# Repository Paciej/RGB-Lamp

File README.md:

# Smart RGB LED Lamp — BLE Controlled (ESP32)

A Bluetooth Low Energy (BLE) controlled RGB LED lamp built on the ESP32 microcontroller.
The lamp supports multiple lighting modes, real-time color and brightness control,
and temperature monitoring — all controllable wirelessly via **nRF Connect** app.
A dedicated mobile application is currently under development.

---

## PCB Design (Eagle)

> Schematic and board layout designed in Eagle CAD.

---

## Printed & Assembled PCB

> Physical PCB after printing and soldering.

---

## Control via nRF Connect

> The lamp is currently controlled using the **nRF Connect** mobile app.
> Temperature readings are exposed as a BLE characteristic and visible directly in the app.

---

##  Lighting Modes

### Random Color — Physical Button
> Press the physical button to apply a random color using ESP32's hardware RNG.

---

### Candle Mode
> Simulates a realistic flickering candle effect.

---

### Pulse Mode
> Smooth brightness breathing effect.

---

### Wave Mode
> Seamless smooth transitions across the full RGB spectrum.

---

##  Features

-  **Full RGB color control** — set any color via BLE (values 0–255 per channel)
-  **Brightness control** via MOSFET PWM (low-side configuration)
-  **Temperature monitoring** — DS18B20 sensor exposed as a BLE characteristic
-  **Random color button** — applies a random color using ESP32's hardware RNG
-  **Lighting modes:**
  - Candle (flicker simulation)
  - Pulse (breathing effect)
  - Wave (smooth RGB transitions)
-  **BLE communication** — controlled via nRF Connect (dedicated app in development)

---

##  Pin Configuration (ESP32 DevKit)

| Pin | Function | Component |
|-----|----------|-----------|
| 23 | Red channel (PWM) | RGB LED — Red |
| 24 | Green channel (PWM) | RGB LED — Green |
| 25 | Blue channel (PWM) | RGB LED — Blue |
| 9 | 1-Wire data | DS18B20 Temperature Sensor |
| 11 | Button input | Random color trigger |

---

##  Hardware Components

| Component | Description |
|-----------|-------------|
| **ESP32 DevKit** | Main microcontroller with built-in BLE |
| **RGB LED 3W (Star)** | High-brightness point light source |
| **MOSFET (×3)** | Low-side PWM drivers for each RGB channel |
| **LM2596 Buck Converter Module** | Steps down 12V supply to 3.3V for ESP32 |
| **DS18B20** | Digital 1-Wire temperature sensor |
| **Resistor 33Ω 5W** | Custom current-limiting resistor |
| **Push Button** | Physical control for random color |

>  The repository includes pre-built external libraries for ESP32 DevKit, DS18B20,
> and the custom 33Ω 5W resistor component (Eagle library).

---

##  Libraries

The project uses the following external libraries bundled in the repository:

- `ESP32 BLE Arduino` — BLE GATT server implementation
- `DallasTemperature` + `OneWire` — DS18B20 sensor support
- Custom Eagle component library — 33Ω 5W resistor footprint

---

## Setup

1. Open the project in **Arduino IDE** or **PlatformIO**
2. Select board: `ESP32 Dev Module`
3. Install libraries from the `/libraries` folder (or use the bundled ones)
4. Flash the firmware to your ESP32
5. Open **nRF Connect** on your mobile device
6. Scan for the device and connect
7. Use GATT characteristics to:
   - Write RGB values (3 bytes: R, G, B)
   - Write lighting mode
   - Read temperature

---

##  BLE Control (nRF Connect)

Until the dedicated app is released, the lamp can be fully controlled via **nRF Connect**:

- Write `[R, G, B]` bytes to the color characteristic to set color
- Write a mode byte to switch lighting modes:
  - `Candle` — Candle
  - `Pulse` — Pulse
  - `Wave` — Wave
- Read the temperature characteristic to monitor the LED temperature

---

##  Project Info

- **University:** Silesian University of Technology
- **Faculty:** Faculty of Automatic Control, Electronics and Computer Science
- **Subject:** Microprocessor and embedded systems
- **Author:** Maciej Porębski

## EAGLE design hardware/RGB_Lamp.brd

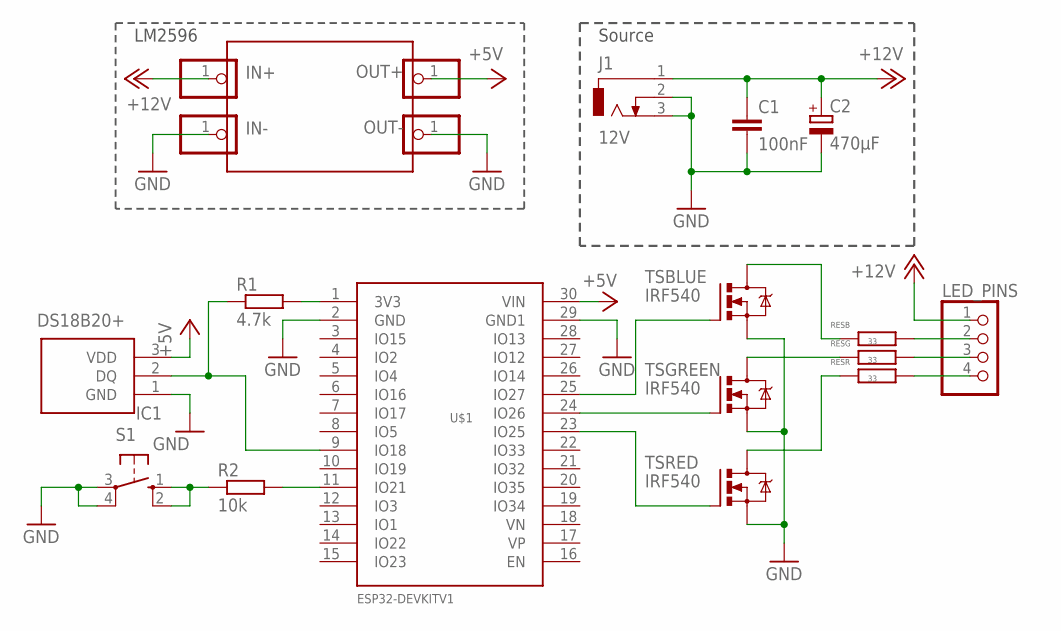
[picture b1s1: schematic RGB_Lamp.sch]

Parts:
C1: 100nF; C050-025X075
C2: 470μF; E3,5-8
IC1: DS18B20+; DS18B20
IN+: PINHD-1X1; 1X01
IN-: PINHD-1X1; 1X01
J1: 12V; DCJ0303
LED_PINS: PINHD-1X4; 1X04
OUT+: PINHD-1X1; 1X01
OUT-: PINHD-1X1; 1X01
R1: 4.7k; 0207/10
R2: 10k; 0207/10
RESB: 33; 0922/22
RESG: 33; 0922/22
RESR: 33; 0922/22
S1: 10-XX; B3F-10XX
TSBLUE: IRF540; TO220BV
TSGREEN: IRF540; TO220BV
TSRED: IRF540; TO220BV
U$1: ESP32DEVKITV1; ESP32-DEVKITV1

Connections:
+5V: IC1.3 (VDD), OUT+.1, U$1.30 (VIN)
+12V: C1.1, C2.+, IN+.1, J1.1, LED_PINS.1
B: RESR.1, TSRED.D
GND: C1.2, C2.-, IC1.1 (GND), IN-.1, J1.2, J1.3, OUT-.1, S1.3, S1.4 (P1), TSBLUE.S, TSGREEN.S, TSRED.S, U$1.2 (GND), U$1.29 (GND1)
unnamed: R2.1, S1.1 (S), S1.2 (S1)
unnamed: IC1.2 (DQ), R1.1, U$1.9 (IO18)
unnamed: RESG.1, TSGREEN.D
unnamed: R2.2, U$1.11 (IO21)
unnamed: LED_PINS.2, RESB.2
unnamed: LED_PINS.3, RESG.2
unnamed: LED_PINS.4, RESR.2
unnamed: TSRED.G, U$1.23 (IO25)
unnamed: TSGREEN.G, U$1.24 (IO26)
unnamed: TSBLUE.G, U$1.25 (IO27)
unnamed: R1.2, U$1.1 (3V3)
R: RESB.1, TSBLUE.D

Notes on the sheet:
LM2596
Source

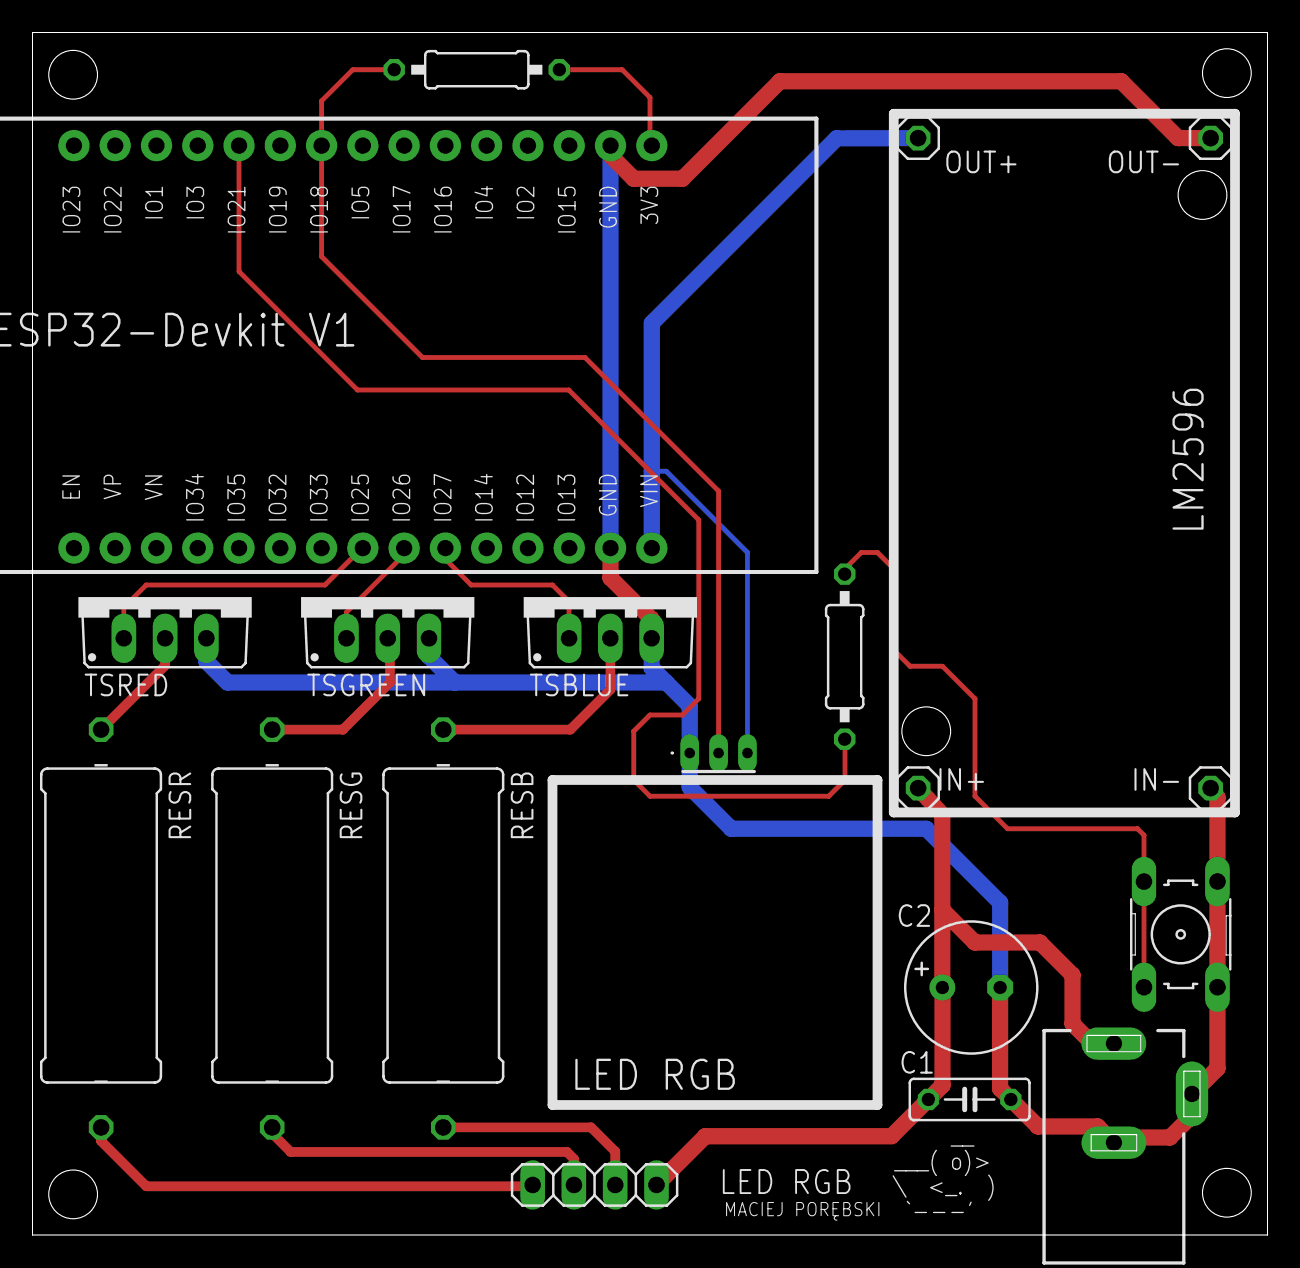
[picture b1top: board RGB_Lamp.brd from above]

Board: 2 copper layers, 76.0 x 74.0 mm, 19 parts (0 on the bottom side), 16 nets.

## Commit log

2026-02-25 Add all code files
2026-03-11 Add schematic and board files
2026-03-11 Add external/custom libraries
2026-03-11 Add additional pictures and screenshots
2026-03-11 Add README for Smart RGB LED Lamp project
    Added detailed project description, features, and setup instructions for the Smart RGB LED Lamp.
2026-03-11 Fix image links in README.md
2026-03-11 Update README with improved formatting and content
2026-03-11 Refactor README for image display and formatting
    Updated README to use HTML img tags for images and improved formatting.
2026-03-11 Enhance README with Lighting Modes and descriptions
    Added sections for Lighting Modes and detailed descriptions for each mode including images.
2026-03-11 Replace demo images for color and mode features
    Updated demo images for various modes in the README.
